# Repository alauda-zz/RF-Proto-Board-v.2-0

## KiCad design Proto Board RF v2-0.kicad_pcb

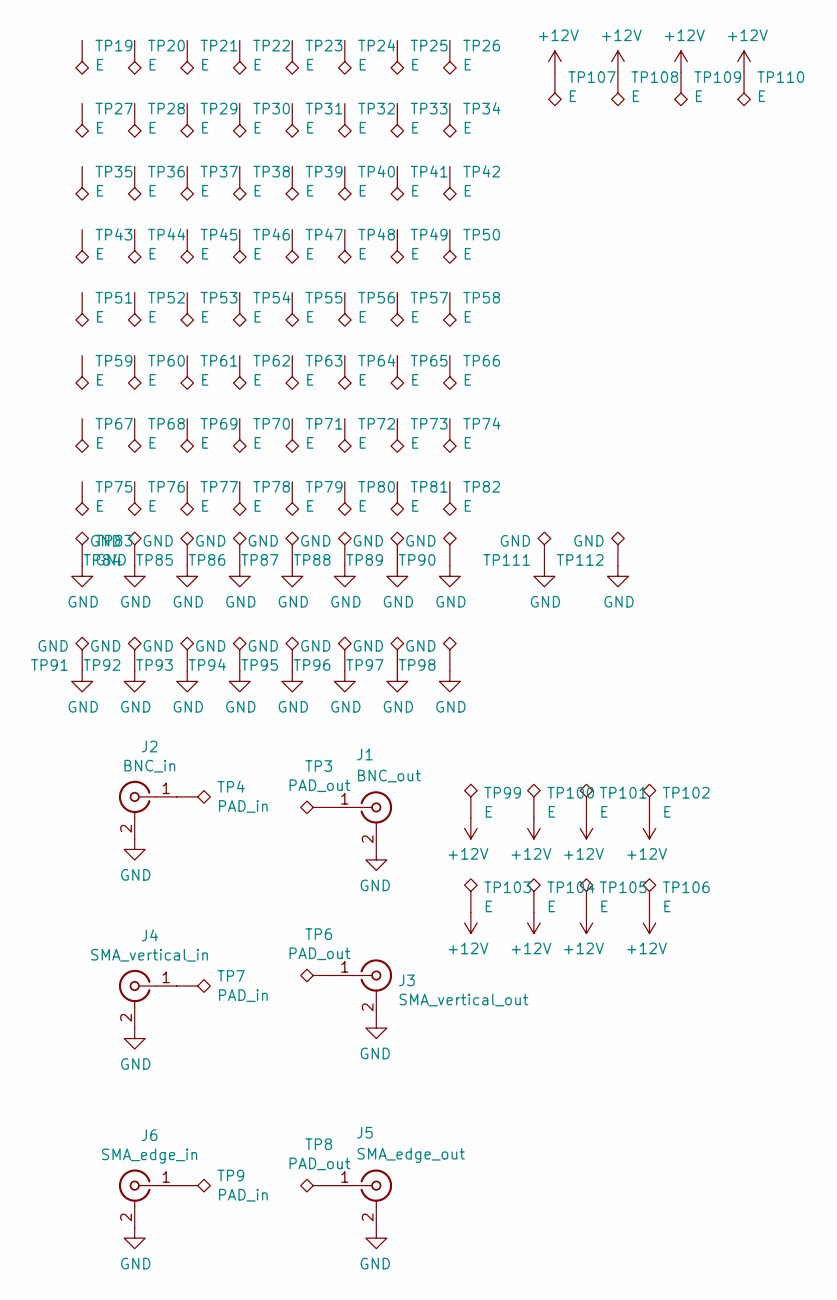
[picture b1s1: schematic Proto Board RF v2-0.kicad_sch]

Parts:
J1: BNC_out; BNC_Amphenol_B6252HB-NPP3G-50_Horizontal
J2: BNC_in; BNC_Amphenol_B6252HB-NPP3G-50_Horizontal
J3: SMA_vertical_out; SMA_Amphenol_901-144_Vertical
J4: SMA_vertical_in; SMA_Amphenol_901-144_Vertical
J5: SMA_edge_out; SMA_Molex_73251-1153_EdgeMount_Horizontal
J6: SMA_edge_in; SMA_Molex_73251-1153_EdgeMount_Horizontal
TP3, TP6, TP8: PAD_out; TestPoint_Pad_4.0x4.0mm
TP4, TP7, TP9: PAD_in; TestPoint_Pad_4.0x4.0mm
TP19, TP20, TP21, TP22, TP23, TP24, TP25, TP26, TP27, TP28, TP29, TP30, TP31, TP32, TP33, TP34, TP35, TP36, TP37, TP38, TP39, TP40, TP41, TP42, TP43, TP44, TP45, TP46, TP47, TP48, TP49, TP50, TP51, TP52, TP53, TP54, TP55, TP56, TP57, TP58, TP59, TP60, TP61, TP62, TP63, TP64, TP65, TP66, TP67, TP68, TP69, TP70, TP71, TP72, TP73, TP74, TP75, TP76, TP77, TP78, TP79, TP80, TP81, TP82, TP99, TP100, TP101, TP102, TP103, TP104, TP105, TP106: E; TestPoint_Pad_4.0x4.0mm
TP83, TP84, TP85, TP86, TP87, TP88, TP89, TP90, TP91, TP92, TP93, TP94, TP95, TP96, TP97, TP98: GND; TestPoint_Pad_4.0x4.0mm
TP107, TP108, TP109, TP110: E; TestPad_2x49-72
TP111, TP112: GND; TestPad_2x103-06

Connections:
+12V: TP99.1, TP100.1, TP101.1, TP102.1, TP103.1, TP104.1, TP105.1, TP106.1, TP107.1, TP108.1, TP109.1, TP110.1
GND: J1.2 (Ext), J2.2 (Ext), J3.2 (Ext), J4.2 (Ext), J5.2 (Ext), J6.2 (Ext), TP83.1, TP84.1, TP85.1, TP86.1, TP87.1, TP88.1, TP89.1, TP90.1, TP91.1, TP92.1, TP93.1, TP94.1, TP95.1, TP96.1, TP97.1, TP98.1, TP111.1, TP112.1
unnamed: J1.1 (In), TP3.1
unnamed: J2.1 (In), TP4.1
unnamed: J3.1 (In), TP6.1
unnamed: J4.1 (In), TP7.1
unnamed: J5.1 (In), TP8.1
unnamed: J6.1 (In), TP9.1

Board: 2 copper layers, 106 parts (0 on the bottom side), 8 nets, no tracks yet.

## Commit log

2022-11-23 Initial
2022-11-23 Creat un test pad de 6x6 mm
2022-11-23 Înlăturat toate fișierele .DS_Store
2022-11-23 Adăugat pad de 10x10mm
2022-11-23 Adăugat schemă în pdf
